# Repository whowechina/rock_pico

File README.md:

# Rock Pico - Rock Fever Style Mini Controller
[点这里可以切换到中文版](README_CN.md)

## Features
* Cool thin design.
* Foldable with soft hinge.
* Very easy to build.
* All source files open.

## Thanks
Thanks to many respectful guys/companies who made their tools or materials free or open source (KiCad, OnShape, InkScape, Raspberry things).

Special thanks to community projects and developers.
And also this project:
* RP_Silicon_KiCad: https://github.com/HeadBoffin/RP_Silicon_KiCad

## My Other Projects
You can check out my other cool projects.

* Popn Pico: https://github.com/whowechina/popn_pico
* IIDX Pico: https://github.com/whowechina/iidx_pico
* Chu Pico: https://github.com/whowechina/chu_pico
* Mai Pico: https://github.com/whowechina/mai_pico
* Diva Pico: https://github.com/whowechina/diva_pico
* AIC Pico: https://github.com/whowechina/aic_pico
* Groove Pico: https://github.com/whowechina/groove_pico
* Geki Pico: https://github.com/whowechina/geki_pico
* Musec Pico: https://github.com/whowechina/musec_pico
* Ju Pico: https://github.com/whowechina/ju_pico
* Bishi Pico: https://github.com/whowechina/bishi_pico
* Nos Pico: https://github.com/whowechina/nos_pico
* Voltex Pico: https://github.com/whowechina/voltex_pico
* Chord Pico: https://github.com/whowechina/chord_pico
* Dance Pico: https://github.com/whowechina/dance_pico
* Arcade Pico: https://github.com/whowechina/arcade_pico
* Rock Pico: https://github.com/whowechina/rock_pico

## **Disclaimer** ##
I made this project in my personal time with no financial benefit or sponsorship. I will continue to improve the project. I have done my best to ensure that everything is accurate and functional, there's always a chance that mistakes may occur. I cannot be held responsible for any loss of your time or money that may result from using this open source project. Thank you for your understanding.

## About the License
It's CC-NC. So DIY for yourself and for your friend, don't make money from it. And plagiarism that doesn’t even dare to mention the original author is not acceptable. Please note that pooling orders and group buying for raw materials is acceptable.Selling any leftover components at cost (without profit) is also acceptable.

If you're interested in buying from me, or for commercial use, please contact me (Discord, QQ group, Goofish).
* My Discord Invitation: https://discord.gg/M8f2PPQFEA
* QQ Group: 854535476
* Goofish: whowe12345

## HOW TO BUILD
### PCB and Components
* Main PCB, Just go [JLC](https://jlcpcb.com/) or some other PCB vendor you like and make an order, make sure the board thickness is **1.6mm**. You need 2 boards for the build.
* 1x Raspberry Pi Pico (a clone with type-C port is better).
* 7x Kailh Choc v1 or v2 key switches, I suggest using heavy ones.  
  https://www.kailhswitch.com/mechanical-keyboard-switches/low-profile-key-switches/burnt-orange-switch.html  
  https://www.kailhswitch.com/mechanical-keyboard-switches/key-switches/kailh-low-profile-switch-choc-v2.html
* 21x reverse mount WS2812B-3528 (or WS2812B-2835) RGB LEDs.
* 7x 0603 0.1uF capacitors.
* 4x SH1.0 3P horizontal surface mount connector.
* 1x PJ-342 surface mount 3.5mm audio jack.  
  https://www.lcsc.com/product-detail/C668606.html

### Other Components
* 12x M2.5\*5mm\*3.5mm (length\*outer diameter) heatset inserts.
* 12x M2.5\*(10-11)mm flat head screws.
* 8x 2U U-shape stabilizer steels.
* 4x 3U U-shape stabilizer steels.
* 2x SH1.0 3P silicone cables, pin-to-pin straight-through (also called reverse orientation), 10cm in length.
* 1x Silicone tube, 38mm inner diameter, 40mm outer diameter, cut to 48mm length.
* 12x Silicone anti-slip round pads, 12mm diameter, 2-3mm thickness.

* 2x 60mm round flat (or slight dome) arcade buttons, clear or white color, to salvage the transparent button caps. Buttons in the following link look good, but not validated.  
  https://www.amazon.com/dp/B07XYVP62V/ref=twister_B08HH6X31D

* 4x 46mm round flat arcade buttons, clear or white color, to salvage the transparent button caps. Buttons in the following link look good, but not validated.  
  https://www.amazon.com/uxcell-Button-Illuminated-Switch-Arcade/dp/B07XYWXLS9

* Optional: 2x 0.3mm\*5mm\*10mm (wire diameter\*outer diameter\*length) springs, to increase main button force.

### Step 1 - Soldering
* Solder 2 PCBs for left side and right side. Apply thin insulating tape at the back of the Pi Pico before soldering, but don't cover the pins. This is how they looks (left top, right top, left bottom, right bottom).  

### Step 2 - 3D Print
* Base parts (`BaseLeft.3mf` and `BaseRight.3mf`), black, no support.
* Panel parts (`PanelLeft.3mf` and `PanelRight.3mf`), use support. Multi-color, silk silver for the main body, black, blue and red for the patterns.
* Button seats (`Button*_Chocx.3mf`), print upside down, with supports on build plate only. Choose the version that matches your key switch. Multi-color, PLA Tough white is recommended for the main body, Silk gold and Silk white for the main patterns, Black for pattern outlines (ButtonA and ButtonB), and red for background on START button (ButtonC).
* Hinge hole helper (`Hinge Hole Helper.stl`), used to accurately align and punch hinge holes.

### Step 3 - Assembly
* Use proper tool to install heatset inserts into the base parts.
* Punch hinge holes on the silicone tube using the hinge hole helper.
* Connect left and right side PCBs using the SH1.0 cables. Make sure the cables go through the hinge tube.
* Route the two cables along the edge of the tube for a neat appearance and then securely hook the hinge tube onto the posts on left and right base parts. 
* Align the left and right side PCBs and push them down into the base parts until they are seated securely.
* Install the buttons on to the key switches and then install 2 U-shape stabilizer steels for each button (except the START button), they should be perpendicular to each other. For the red large button, you can place an optional spring before installation to increase the force.
* Push the button caps (salvaged from the original arcade buttons) onto the buttons until you hear or feel them click into place.
* This is how it looks now.  
  
* Put on the panels and secure them with M2.5 flat head screws.
* Apply the anti-slip pads to the bottom of the base parts to prevent sliding during use.
* The 3.5mm audio jack is for external pedal. A cheap digital keyboard sustain pedal is a suitable choice.

### Firmware
* The UF2 file is in the `Production/firmware` folder.
* For the new build, hold the BOOTSEL button while connect the USB to a PC, there will be a disk named "RPI-RP2" showed up. Drag the UF2 firmware binary file into it and that's it. There's a small hole at the back side of the keyboard, it is facing right to the BOOTSEL button.
* If it's already running the firmware, hold all four buttons (START + RED + left BLUE + right BLUE) while plugging in the USB to enter the firmware update mode.

* At the left panel, while plugging in the USB:
  * Hold START + RED button to enable both Joystick and Keyboard input.
  * Hold START + left BLUE button to enable only Joystick input.
  * Hold START + right BLUE button to enable only Keyboard input.

* You can set the button LED brightness using `level` command in CLI.

### Tools I Made
* Gamepad test - You can use it to check if all buttons and axes are working correctly.   
  https://whowechina.github.io/iidx_pico/Tools/gamepad_test.html
* Command-line tool - You can access controller's built-in CLI port using this tool.  
  https://whowechina.github.io/iidx_pico/Tools/cli_tool.html

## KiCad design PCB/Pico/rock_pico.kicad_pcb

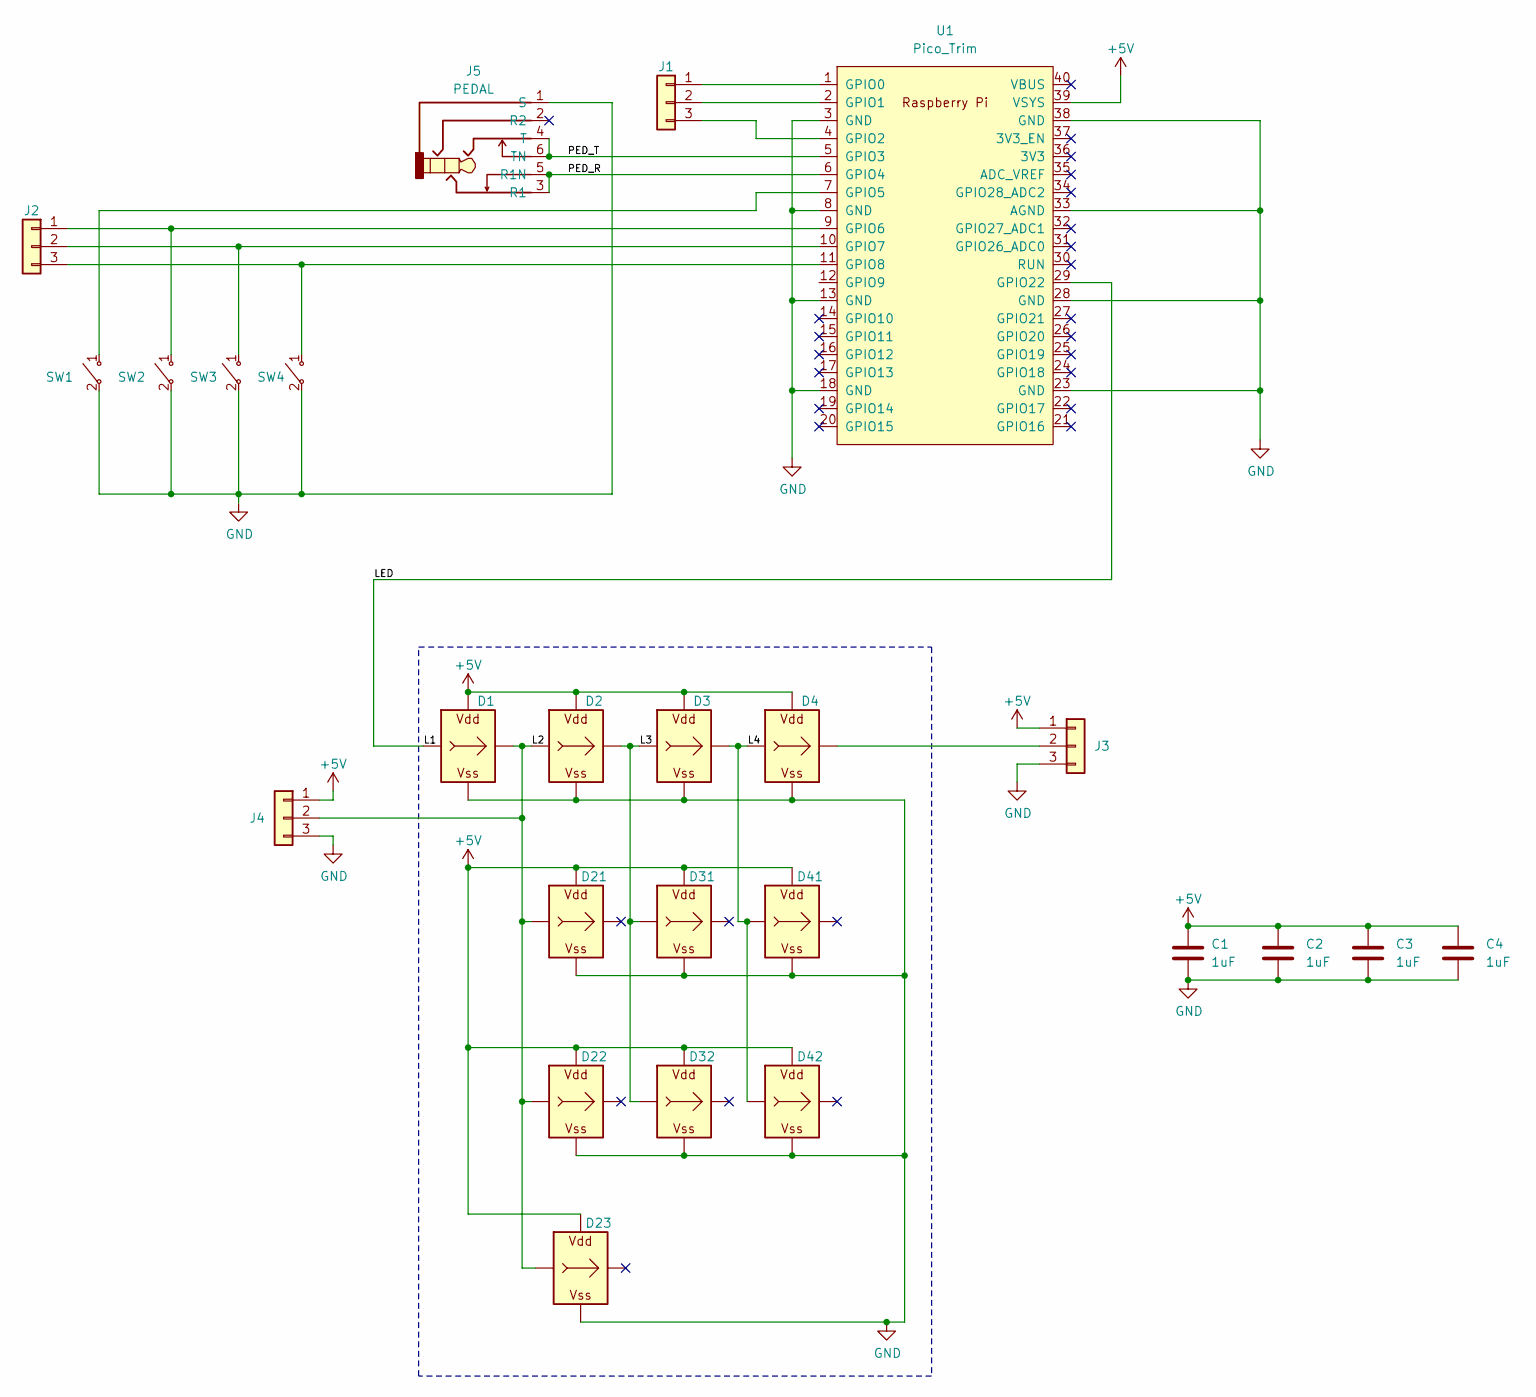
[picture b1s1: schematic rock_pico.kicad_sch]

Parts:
C1, C2, C3, C4: 1uF; C_0603_1608Metric_Pad1.08x0.95mm_HandSolder
D1, D2, D3, D4, D21, D22, D23, D31, D32, D41, D42: WS2812B_Unified; WS2812B-2835_EMBED
J1, J2: ExtBT; SH1.0_3P_Solder_Combo
J3, J4: LED; SH1.0_3P_Solder_Combo
J5: PEDAL; PJ342
SW1: Aux1; SW_Kailh_Choc_V1V2_1.00u_2LED
SW2: Aux2; SW_Kailh_Choc_V1V2_1.00u_2LED
SW3: B1; SW_Kailh_Choc_V1V2_1.00u_2LED
SW4: B5; SW_Kailh_Choc_V1V2_1.00u_2LED
U1: Pico_Trim; RPi_Pico_SMD_No_USB

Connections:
+5V: C1.1, C2.1, C3.1, C4.1, D1.V (VDD), D2.V (VDD), D3.V (VDD), D4.V (VDD), D21.V (VDD), D22.V (VDD), D23.V (VDD), D31.V (VDD), D32.V (VDD), D41.V (VDD), D42.V (VDD), J3.1, J4.1, U1.39 (VSYS)
/L1: D1.I (In), U1.29 (GPIO22)
/L2: D1.O (Out), D2.I (In), D21.I (In), D22.I (In), D23.I (In), J4.2
/L3: D2.O (Out), D3.I (In), D31.I (In), D32.I (In)
/L4: D3.O (Out), D4.I (In), D41.I (In), D42.I (In)
/PED_R: J5.3 (R1), J5.5 (R1N), U1.6 (GPIO4)
/PED_T: J5.4 (T), J5.6 (TN), U1.5 (GPIO3)
GND: C1.2, C2.2, C3.2, C4.2, D1.G (VSS), D2.G (VSS), D3.G (VSS), D4.G (VSS), D21.G (VSS), D22.G (VSS), D23.G (VSS), D31.G (VSS), D32.G (VSS), D41.G (VSS), D42.G (VSS), J3.3, J4.3, J5.1 (S), SW1.2 ("~"), SW2.2 ("~"), SW3.2 ("~"), SW4.2 ("~"), U1.3 (GND), U1.8 (GND), U1.13 (GND), U1.18 (GND), U1.23 (GND), U1.28 (GND), U1.33 (AGND), U1.38 (GND)
unnamed: D4.O (Out), J3.2
unnamed: J1.1, U1.1 (GPIO0)
unnamed: J1.2, U1.2 (GPIO1)
unnamed: J1.3, U1.4 (GPIO2)
unnamed: J2.1, SW2.1 ("~"), U1.9 (GPIO6)
unnamed: J2.2, SW3.1 ("~"), U1.10 (GPIO7)
unnamed: J2.3, SW4.1 ("~"), U1.11 (GPIO8)
unnamed: SW1.1 ("~"), U1.7 (GPIO5)

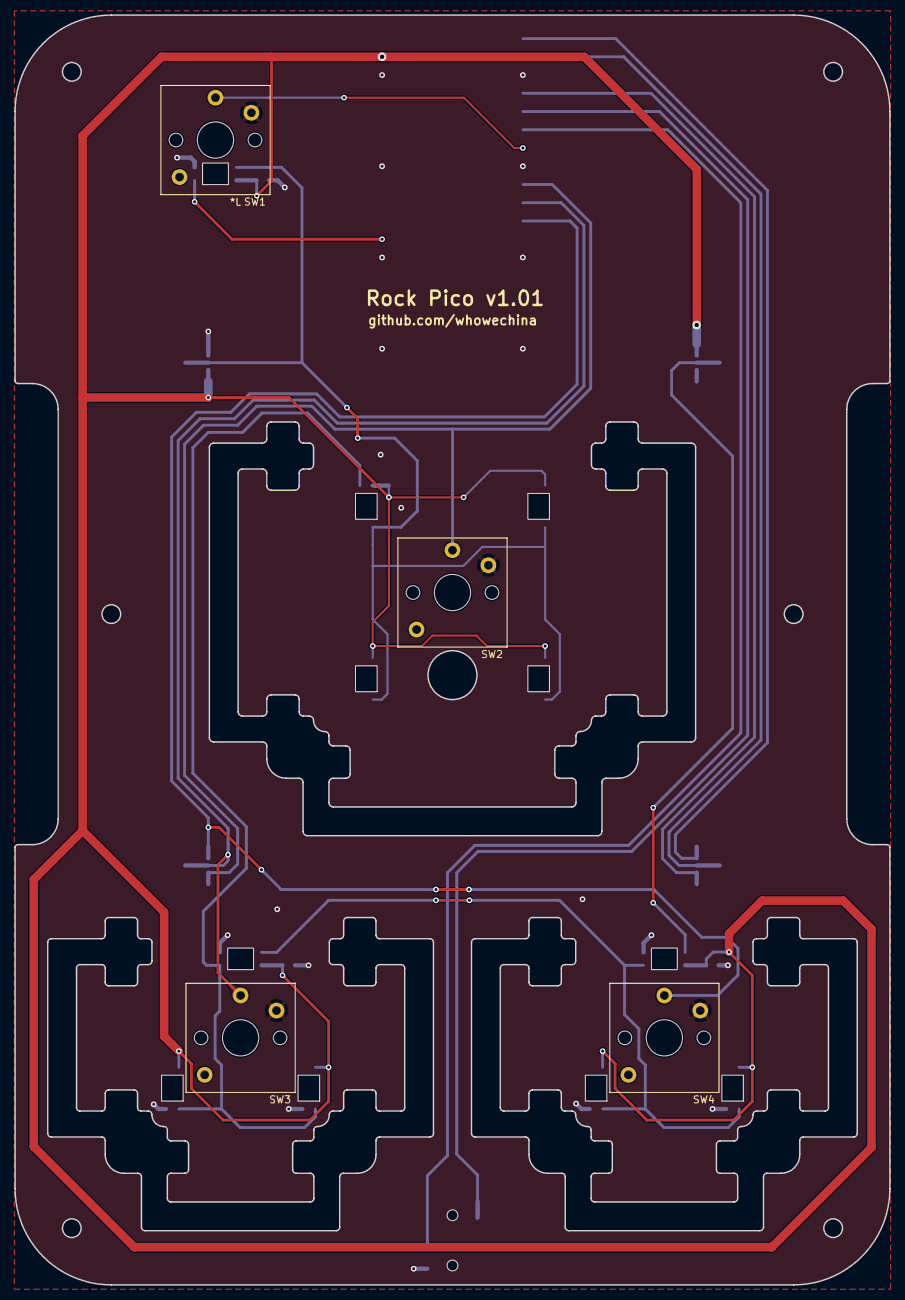
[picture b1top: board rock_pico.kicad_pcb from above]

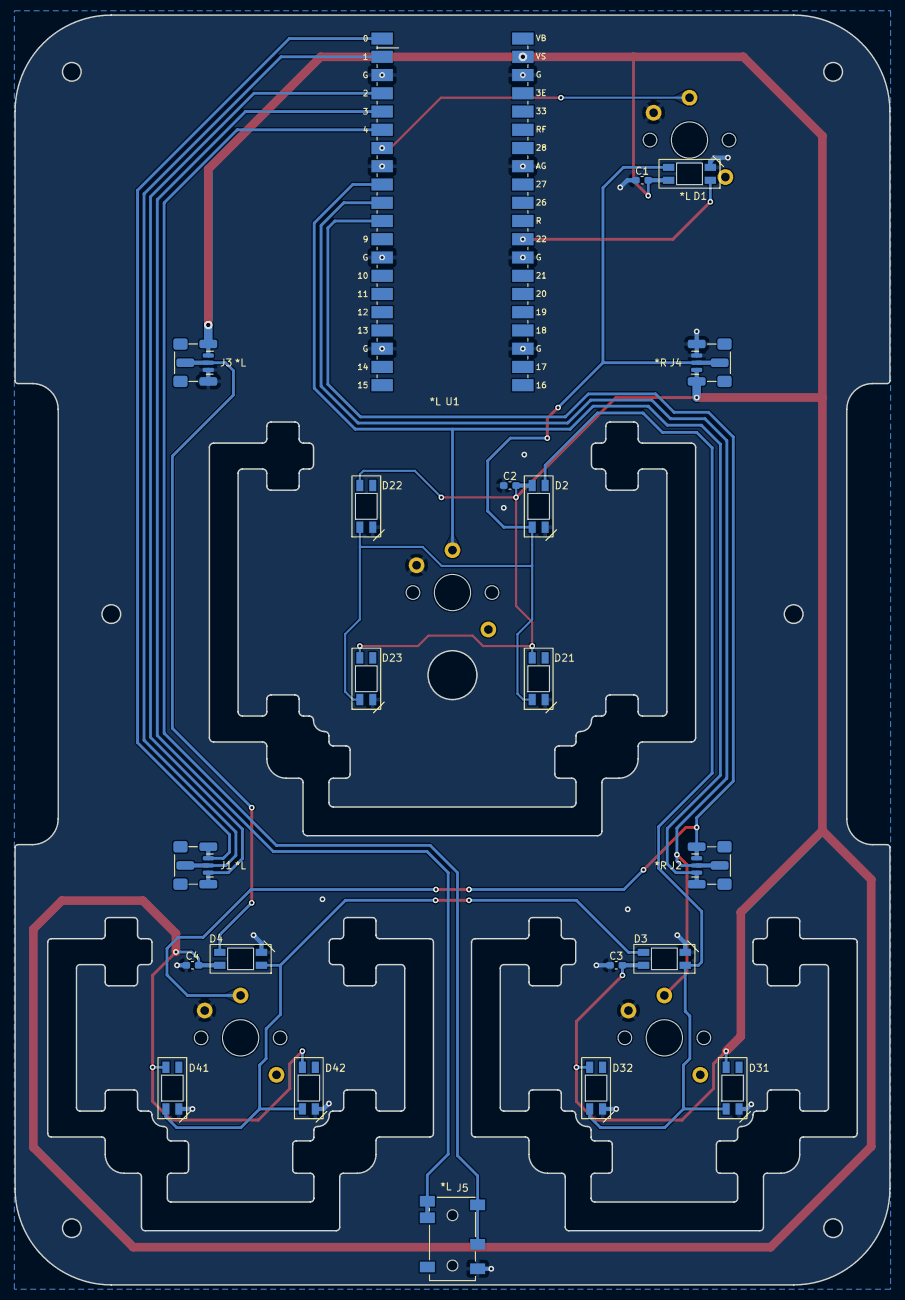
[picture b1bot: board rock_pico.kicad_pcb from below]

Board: 2 copper layers, 121.8 x 176.8 mm, 25 parts (21 on the bottom side), 16 nets.
